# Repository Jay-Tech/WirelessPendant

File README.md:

# Wireless Pendant

Firmware for a wireless handwheel pendant for a grblHAL machine, and for the
receiver board that carries it to the PC. The sender application it talks to is
a separate project — [Jay-Tech/GrblHAL-Sender](https://github.com/Jay-Tech/GrblHAL-Sender),
whose [Wireless Pendant](https://github.com/Jay-Tech/GrblHAL-Sender#wireless-pendant)
section covers the settings at that end. What crosses between them is
[the wire protocol](micropython/pendant/protocol.py) — newline-delimited JSON,
the same either way it travels.

Two boards, both **ESP32-S3**:

| | |
|---|---|
| **pendant** | the handheld — encoder wheel, touch screen, battery. Waveshare ESP32-S3-Touch-LCD-3.5 |
| **receiver** | plugs into the sender's PC, presents a serial port, talks ESP-NOW to the pendant |

The pendant reaches the sender two ways. Over **ESP-NOW** it talks to the
receiver board, which needs no network and no credentials — this is the one it
is built around, because an open-source pendant cannot require the builder to
have usable WiFi in their shop. Over **WiFi** it joins the shop network and
opens a TCP session to the sender directly; that path stays because it is the
reference every jog constant was fitted against.

New board? → [Setting up a board](#setting-up-a-board). One command.

## The hardware

Three things, and none of them is a breadboard any more: an all-in-one host
board, a passive PCB that breaks its header out, and a printed enclosure. All of
it lives under [`hardware/`](hardware/).

| | | |
|---|---|---|
| **host board** | bought | [Waveshare ESP32-S3-Touch-LCD-3.5](https://www.waveshare.com/esp32-s3-touch-lcd-3.5.htm?sku=30733) — MCU, display, touch, PMIC and radio on one board |
| **PSB v1.0** | [`hardware/PendantPcb/`](hardware/PendantPcb/) | breaks that board's 32-pin header out to the handwheel and the three buttons. Carries no components at all |
| **enclosure** | [`hardware/CADandSTL/`](hardware/CADandSTL/) | Fusion 360 sources and printable STLs — the handheld, and a dock for it |

**The bill of materials is five orderable items, with no passives at all:** the
host board, an MPG handwheel, three tactile switches, a LiPo cell, and whatever
the printer eats. A 5 V boost module and the encoder's 22 kΩ divider pair were
both on that list until 2026-08-15 and were measured off it rather than reasoned
off it — [platform-decision.md](hardware/platform-decision.md) carries the
numbers, and [Encoder wiring](#encoder-wiring) below keeps the divider material
for the Pico build and for characterising an unknown wheel.

### The host board

[Waveshare ESP32-S3-Touch-LCD-3.5](https://www.waveshare.com/esp32-s3-touch-lcd-3.5.htm?sku=30733),
SKU 30733.

| | |
|---|---|
| MCU | ESP32-S3R8, dual Xtensa LX7 @ 240 MHz |
| Memory | 512 KB SRAM + **8 MB octal PSRAM**, 16 MB flash |
| Display | 3.5" IPS, 320 x 480, ST7796 over SPI |
| Touch | FT6336U, I²C `0x38`, polled |
| Power | **AXP2101** — charger, power path, fuel gauge and power button in one part, switching rather than linear |
| Battery | 3.7 V LiPo on an MX1.25 header, plus a separate SH1.0 header for an RTC cell |
| Radio | WiFi 4 (2.4 GHz) + BLE 5 on an onboard antenna, **with an IPEX pad for an external one** |
| Unused here | PCF85063 RTC, QMI8658 IMU, ES8311 codec, mic, speaker header, TF slot, camera header |
| Break-out | one 32-pin, 2.54 mm header — which is what PSB v1.0 mates to |

Two of those are why the board won. The **IPEX connector** — reached by
resoldering one resistor — is worth more on a handheld carried around a steel
machine than any latency figure measured here, and the Pico 2 W's antenna is
fixed. The **AXP2101** does in one part what the Pico build needed a LiPo Amigo
Pro and its wiring to do. The 8 MB PSRAM is enough for a full 320x480x2
framebuffer, which is also why the committed MicroPython build is the
`SPIRAM_OCT` variant rather than the plain one — see [ESP32-S3](#esp32-s3).

**The pin map is not in Waveshare's wiki and cannot be read off their schematic
PDF.** It came from their demo code, examples 08 and 11, which agree — and three
of the pins turn out not to be pins:

- **The LCD has no chip select.** The panel is permanently selected, so
  `st7796.py` has to tolerate `cs=None` rather than toggle something that does
  not exist.
- **LCD reset is an I²C write**, to a **TCA9554 expander at `0x20`** that is not
  in the board's advertised feature list and answers writes but not reads. The
  driver takes a reset *callable* instead of a pin, so the caller supplies either
  a pin toggle or an expander write and the driver stays portable.
- **Touch breaks out neither INT nor RST**, and needs neither, being polled.

Everything else transferred intact — the ST7796 init sequence, MADCTL, `INVON`,
the framebuffer push, and the whole of `screen.py` including the portrait layout,
the DRO digits, the step grid and the probe page. USB-C sits at the bottom edge,
which is where the reference pendant puts its cable, so the enclosure works with
it rather than against it.

An I²C scan of the board reads `0x18` ES8311, `0x20` TCA9554, `0x34` AXP2101,
`0x38` FT6336U, `0x51` PCF85063, `0x6b` QMI8658. That AXP2101 at `0x34` is also
how [`setup.py`](tools/setup.py) tells a pendant from a receiver, since the two
enumerate identically over USB — and it reads the chip ID rather than pinging the
address, so something else answering there is not mistaken for a battery.

> **The AXP2101's fuel gauge is not to be trusted on this board**, and the
> pendant does not use it. See [Battery and backlight](#battery-and-backlight)
> for what it did and what replaced it.

### PSB v1.0 — the breakout PCB

[`hardware/PendantPcb/`](hardware/PendantPcb/) is the KiCad project, with the fab
output in [`production/`](hardware/PendantPcb/production/).
[daughter-board.md](hardware/daughter-board.md) is the spec and the argument
behind it.

**It is built, and the pendant runs on it** — this is a board in service rather
than a drawing. The only difference between the fabricated boards and what is in
the repo is the silkscreen: they were made before the `PSB v1.0` version marking
was added, so they carry the functional labels and no revision. Nothing
electrical differs.

It exists because the host board brings almost everything out on that one
header, so a single mating board reaches every signal the pendant needs. The
alternative is seven flying leads soldered to a header, in a tool that gets
carried around a shop.

**Seven signals, and no components.** The move to a 3V3 encoder removed the last
two resistors it would have carried.

| Net | GPIO | J2 pin | Goes to |
|---|---|---|---|
| Encoder A | **9** | 14 | J3 pin 3 — direct, no resistor |
| Encoder B | **10** | 12 | J3 pin 4 — direct, no resistor |
| Encoder Vcc | — | 32 | J3 pin 1. **+3V3, measured 3.29 V — not 5 V, not VBAT** |
| Encoder 0V | — | 4, 30 | J3 pin 2 |
| `feed_hold` | **38** | 7 | SW1, silkscreened `HOLD` |
| `cycle_start` | **39** | 9 | SW2, silkscreened `START` |
| `zero_axis` | **40** | 11 | SW3, silkscreened `ZERO`, long hold |

The GPIO column was measured on the assembled handheld, 2026-08-16, and matches
`BUTTON_MAP` and `ENCODER_PIN_A/B` in
[`pendant.py`](micropython/pendant/pendant.py) — which is the authority. If
either moves, both have to. Buttons are active low against the S3's internal
pull-ups, with no external pull-ups and no debounce parts;
[`buttons.py`](micropython/pendant/buttons.py) debounces in software and has done
since the Pico build.

**Pin 32 is the one worth a meter.** The whole 3V3 encoder decision rests on it
being a regulated rail: the wheel is open-collector, so its outputs swing to
whatever supplies it, and they reach GP9 and GP10 with nothing in the way. On
VBAT or VBUS that is over the S3's ~3.6 V absolute maximum. 3.29 V says it is the
right rail.

**54.50 x 100.00 mm**, 2 mm chamfers on all four corners, and four drill groups —
which is the acceptance test, because anything outside the set is then visible at
a glance:

| Diameter | Plating | Count | |
|---|---|---|---|
| 0.300 | PTH | 2 | vias |
| 1.000 | PTH | 36 | 32 header + 4 encoder |
| 1.300 | PTH | 6 | three switches, two pads each |
| 2.200 | NPTH | 6 | mounting |

A missing 1.300 group means the switches were placed after the export — which
happened, and produced a zip with no buttons on it at all.

Two things on the board are deliberate traps, and both are cheap to check:

- **`+BATT` at J2 pin 1 is a single-node net** — that pad and nothing else on the
  board. Mate the boards and probe it: battery voltage means the numbering
  composes correctly through symbol, footprint and placement; 0 V or 3.3 V means
  one of those three mirrors did not cancel. Safe to probe precisely because
  nothing else is on it.
- **J3 has no keying**, and carries 3V3 and GND adjacent to each other. A cable
  fitted backwards puts reverse polarity across the wheel, so the `+ - A B`
  silkscreen and the pin 1 mark are load-bearing rather than decorative.

The three switches sit **19.0 mm apart, centred on the board's own centreline**.
The first layout had them at 19.5 and 18.5 with the middle one 0.5 mm off, and
unequal spacing between three caps is visible every time once the enclosure is
on.

A **reverse-polarity guard** for the battery is a second, smaller board. It shares
no net with PSB v1.0, which is why it is not on it, and
[daughter-board.md](hardware/daughter-board.md) has the circuit, what to buy, and
how to prove it before it meets the host board. Its KiCad project is gitignored,
so that specification is the only copy of it a clone gets.

### Printed parts

[`hardware/CADandSTL/`](hardware/CADandSTL/). Each folder holds one Fusion 360
file and the STLs exported from it — the `.f3d` is the source and the thing to
edit, the STLs are what a slicer wants. Sizes below are each mesh's measured
bounding box.

**The handheld** — [`Pendant/`](hardware/CADandSTL/Pendant/), from `Pendant.f3d`:

| File | Size, mm | |
|---|---|---|
| `Pendant.stl` | 70.00 x 27.65 x 186.00 | the body |
| `PcbCover.stl` | 54.70 x 3.16 x 100.00 | closes over PSB v1.0 — the footprint is that board's 54.50 x 100.00 plus clearance |
| `BatteryCover.stl` | 65.60 x 8.50 x 75.16 | the cell bay |
| `Button1.stl` | 10.80 x 10.64 x 8.80 | a cap for one of the three switches |
| `Button3.stl` | 10.80 x 10.64 x 8.80 | same envelope, different geometry |
| `ButtonUsbV2.stl` | 13.00 x 10.54 x 8.80 | the wider cap |
| `PowerButton.stl` | 8.39 x 3.60 x 4.60 | reaches the AXP2101's power button through the shell |

**The dock** — [`Mount/`](hardware/CADandSTL/Mount/), from `Mount.f3d`:

| File | Size, mm | |
|---|---|---|
| `Mount.stl` | 82.00 x 37.09 x 102.00 | the cradle the pendant sits in |
| `MountBase.stl` | 82.00 x 37.09 x 10.00 | its base, same footprint |
| `MountUsb.stl` | 20.00 x 20.00 x 5.90 | carries the USB-C end |
| `MountUsbLock.stl` | 11.70 x 6.10 x 17.70 | retains it |

**The body is 186 mm in its longest axis**, so it wants a bed with at least that
much in one direction — a 220 mm printer is fine, a 180 mm one is not.

**The button caps are one dimension chain, not three independent choices.** The
header fixes PSB v1.0's position relative to the host board in all three axes,
and the caps have to reach the enclosure top from there — so board stack height,
switch height and cap height are a single sum. The requirement the caps are cut
against is that each one **bottoms on the enclosure** at the end of its stroke
rather than on the switch, so the switch never takes the force of a gloved thumb,
and that the plunger is guided by a bore in the shell rather than by a spacer
resting on the board. [daughter-board.md](hardware/daughter-board.md) has the
reasoning; `Pendant.f3d` is where to check it.

## Why there is a Pico in here

The project started on a Raspberry Pi Pico 2 W, and that board is still on the
bench as `pico` — it is the reference the ESP32 gets compared against when
something feels wrong, which is why the notes below are kept rather than
deleted. Nothing shipping runs on it.

## Pico 2 W board notes

| | |
|---|---|
| MCU | RP2350, dual Cortex-M33 @ 150 MHz **or** dual Hazard3 RISC-V |
| RAM / flash | 520 KB SRAM / 4 MB QSPI |
| PIO | 3 blocks, 12 state machines |
| Radio | WiFi 4 (802.11n, 2.4 GHz) + Bluetooth 5.2 |
| Power | 1.8-5.5 V into VSYS via onboard buck-boost |

Three things that bite people on this specific board:

- **The onboard LED is not a GPIO.** It hangs off the CYW43 radio chip, so it's
  `Pin("LED")`, never `Pin(25)`. Most Pico tutorials assume a non-W board and
  will silently do nothing.
- **GP29 belongs to the WiFi SPI**, so the usable ADC channels are GP26/27/28
  (channels 0-2). Channel 4 is the internal temperature sensor.
- **Erratum RP2350-E9.** On the A2 stepping, an input pin can latch near 2.15 V
  instead of reading low, and the internal pull-downs are too weak to fix it.
  This hits PIO input programs too. Use an external pull-down of 8.2 kΩ or
  smaller. Stepping A4 corrects it — worth checking which one your board has
  before you spend an evening debugging a "broken" input.

## Setting up a board

```bash
python tools/setup.py
```

One command from a blank ESP32-S3 to a working pendant or receiver. It asks
what you are setting up, finds the board, flashes MicroPython if the board
needs it, checks the hardware matches the role, collects the WiFi and transport
settings, installs, restarts the board and reads back what it says on the way
up.

```bash
python tools/setup.py --pendant     # the handheld
python tools/setup.py --receiver    # the board at the sender's PC
python tools/setup.py --list        # what is attached, and what each one is
```

It replaces the two steps that used to be source edits: `BOARDS` in
[`tools/board.py`](tools/board.py) and a hand-filled `secrets.py`. **If you are
building this for the first time, this is the only thing you need to run** —
everything below is the manual equivalent, kept because it is what to fall back
on when a step misbehaves.

Two things worth knowing about how it finds boards:

- **It never opens a device it has not identified.** Only two USB descriptors
  are eligible — MicroPython on an S3 and on a Pico. Everything else is listed
  and skipped, and a grblHAL controller is named in that listing so you can see
  it was seen and left alone. This matters more than it sounds: `mpremote
  connect auto` once grabbed the STM32 controller on this bench and sent it
  raw-REPL bytes with a machine powered.
- **Each board records what it is**, in a `device.json` written at setup. That
  is what lets a board be found without an entry in `BOARDS`, and it is what
  `sync_board.py --receiver` now checks before it will write `receiver.py` over
  a `main.py` — the pendant and the receiver are both ESP32-S3 and enumerate
  identically, so before this the only guard was a name in a table that a new
  build had not filled in yet.

A pendant board is told apart from a receiver by the **AXP2101 power chip** at
I²C `0x34`, which the pendant carries and a bare receiver does not — and the
chip ID is read rather than the address pinged, so something else answering at
that address is not mistaken for a battery.

Set the receiver up on the sender's PC and it will offer to write the port into
the sender's own config. The sender still never scans for that port itself,
deliberately — see `PendantConfig` for why. This is not scanning; it just
flashed the board and knows where it is.

## Flashing MicroPython

The manual path, and the reference for what `setup.py` does.

### Pico 2 W

1. Download the Pico 2 W `.uf2` from
   [micropython.org/download/RPI_PICO2_W](https://micropython.org/download/RPI_PICO2_W/)
   — take whatever is current there rather than matching the S3 build committed
   at the root, since the two ports version independently. Make sure it's the
   `RPI_PICO2_W` build —
   the plain `RPI_PICO2` build has no WiFi and the plain `RPI_PICO_W` build is
   for the older RP2040 board.
2. Hold **BOOTSEL** while plugging in USB. The board mounts as a drive named
   `RP2350`.
3. Copy the `.uf2` onto it. The board reboots into MicroPython automatically.

If the board misbehaves after switching between Arm and RISC-V builds, or
between MicroPython and C SDK firmware, flash `flash_nuke.uf2` first to wipe
the flash, then reflash. Leftover filesystem blocks confuse the new firmware.

### ESP32-S3

Both the pendant and the receiver are ESP32-S3s, and neither takes a `.uf2` —
there is no BOOTSEL drive to drag a file onto, so flashing goes over the serial
port with `esptool`. The build this repo runs is committed at the root, and it
is the **`SPIRAM_OCT`** variant — these boards have octal SPIRAM, and the plain
`ESP32_GENERIC_S3` build leaves it unused. That mismatch does not fail at the
flash or at the boot; it surfaces much later as an allocation running out while
the pendant paints its display, which reads as a screen bug.

`setup.py` picks that variant on its own when both are sitting at the root, and
asks when it genuinely cannot tell — two versions of the same variant, say,
which is what a version bump leaves behind.

```bash
python -m pip install esptool
```

Put the board into its ROM bootloader: hold **BOOT**, tap **RESET**, release
**BOOT**. It re-enumerates as `303a:1001`, which `tools/board.py` labels
*"ROM bootloader — esptool, not mpremote"*. In MicroPython it is `303a:4001`
instead, and `esptool` will not talk to that one.

Then find the port it came up on — and look it up again rather than reusing what
it had a moment ago. The bootloader and MicroPython present different USB
descriptors, so Windows renumbers the board every time it is flashed. That is
also why every tool here targets a serial number instead of a COM port.

```bash
python -m esptool --chip esp32s3 --port COM# erase-flash
```

```bash
python -m esptool --chip esp32s3 --port COM# --baud 460800 write-flash -z 0 ESP32_GENERIC_S3-SPIRAM_OCT-<version>.bin
```

Offset `0`, not the `0x1000` the original ESP32 takes.

esptool 5 renamed these from `erase_flash` and `write_flash`; the underscore
forms still run but print a deprecation warning, which in the middle of a flash
reads like a fault. `setup.py` picks the spelling from the installed version.

Reset the board and it comes up in MicroPython with a new serial number. Every
S3 here enumerates identically, so that serial number is what distinguishes a
pendant from a receiver, and every tool resolves through it rather than through a
COM port.

There are two places it can come from. `setup.py` writes a `device.json` **on the
board**, which is what lets a board be recognised with no entry in any table —
prefer that. `BOARDS` in [`tools/board.py`](tools/board.py) is the older path and
still works; every id in it is this bench's, so all of them are wrong for you.
`python tools/board.py` lists what is attached and says so when the configured
board is not among them.

## Running the smoke test

Uses [`mpremote`](https://docs.micropython.org/en/latest/reference/mpremote.html):

```bash
pip install mpremote
```

Commands below invoke it as `python -m mpremote` rather than the bare
`mpremote`. On Windows with Microsoft Store Python, the `Scripts\` directory
holding `mpremote.exe` is not on `PATH`, so the bare command fails with
*"not recognized as the name of a cmdlet"* even though the install succeeded.
The `-m` form sidesteps that and works on every platform. See
[PATH fix](#windows-store-python-path) if you want the short command back.

> ### ⚠️ Do not use `connect auto` on a machine with a CNC controller attached
>
> `auto` connects to the first USB serial device it finds. If a grblHAL
> controller is plugged in, that can be the controller rather than the Pico —
> and mpremote will then send raw-REPL control bytes (`Ctrl-A`/`Ctrl-C`) to
> your machine controller trying to get a Python prompt. It happened here: the
> STM32 board on `0483:5740` got grabbed instead of the Pico and reset.
>
> Target the board explicitly by its unique ID instead. The ID is held in one
> place, [`tools/board.py`](tools/board.py), and every tool resolves through it
> — so there is no serial number to copy from a docstring and mistype. It stays
> correct across COM port renumbering.
>
> Run it to see what is attached and which device is the target. It labels the
> controller so it cannot be picked by accident:
>
> ```bash
> python tools/board.py
> ```
>
> Override it without editing anything by setting `PICO_DEVICE`.
>
> Pico boards report a `2e8a:` vendor ID (`0005` = MicroPython running,
> `000f` = RP2350 BOOTSEL). An STM32 grblHAL board reports `0483:5740`. Use
> the serial number in the second column as `id:<serial>`.

Set up credentials (this file is gitignored — it never reaches a commit):

```bash
cp micropython/secrets.example.py micropython/secrets.py
```

**Edit it before running anything.** Leaving the placeholder SSID in place
makes `wifi_join` fail with `no such network in range`. Then copy it to the
board and run the test:

```bash
python tools/sync_board.py
```

```bash
python tools/on_board.py micropython/smoke_test.py
```

`run` streams the script from your PC rather than installing it, but imports
still resolve on the board — which is why `secrets.py` has to be copied over
first. To drop into the REPL instead:

```bash
python -m mpremote connect $PICO_DEVICE repl
```

To confirm the board is seen at all, and check what it's running:

```bash
python -m mpremote devs
```

A Pico 2 W shows a `2e8a:` vendor ID. PID `0005` means MicroPython is already
flashed and talking; PID `000f` means the board is sitting in RP2350 BOOTSEL
mode waiting for a UF2.

Prefer a GUI? [Thonny](https://thonny.org/) works well: set the interpreter to
*MicroPython (Raspberry Pi Pico)* and it handles the board filesystem for you.

### What it checks

Six stages, each reporting PASS / FAIL / SKIP with a summary at the end:

| Stage | Proves |
|---|---|
| `identity` | firmware, chip ID, clock, heap, filesystem |
| `led` | GPIO path via the CYW43 — visible blink |
| `temp` | ADC works (internal sensor, uncalibrated, ±a few °C) |
| `wifi_scan` | radio powers up and hears networks |
| `wifi_join` | association + DHCP lease |
| `net_io` | DNS + TCP + HTTP, end to end |

The last three need `secrets.py`; without it they report SKIP and the rest
still runs, so the script is useful before you've picked a network.

Two of those stages are Pico-shaped: `led` goes through the CYW43 radio chip
rather than a GPIO, and `temp` reads the RP2350's internal sensor. Both are
board-level proof of life rather than anything the pendant depends on — on an S3
the equivalent bring-up is
[`selftest_board.py`](micropython/pendant/selftest_board.py) and the per-subsystem
self-tests under [Pendant hardware summary](#pendant-hardware-summary).

## Pendant hardware summary

Every pin the pendant uses, in one place — the part you want with a soldering
iron in your hand. Why each one is where it is: [The hardware](#the-hardware)
above, and the design notes below.

**Discrete parts: none.** Nothing sits between the host board and the
peripherals — no level shifters, no pull-ups, no dividers, no transistors. The
encoder's 22 kΩ pair left with the move to 3V3, and the display and touch panel
are on the host board rather than wired to it.

| GPIO | Net | Notes |
|---|---|---|
| GP9 | encoder A | direct, no resistor |
| GP10 | encoder B | direct, no resistor |
| GP38 | feed hold | to GND, internal pull-up |
| GP39 | cycle start | to GND, internal pull-up |
| GP40 | zero axis | to GND, internal pull-up, long hold |
| GP1 / GP2 / GP5 | LCD MOSI / MISO / SCK | SPI2, all on the host board |
| GP3 | LCD DC | |
| GP6 | LCD backlight | PWM — see [Battery and backlight](#battery-and-backlight) |
| — | LCD CS | there isn't one; the panel is permanently selected |
| — | LCD RST | TCA9554 at `0x20`, pin 1 |
| GP8 / GP7 | I²C SDA / SCL | I2C0 — touch, PMIC, RTC and IMU all share it |
| **3V3** | encoder Vcc | **not 5 V, not VBAT.** J2 pin 32, measured 3.29 V |
| GND | encoder 0V | J2 pins 4 and 30 |

Deliberately unconnected on PSB v1.0: **J2 pin 2 (VBUS)**, which measures 0 V
without USB and 4.89 V with, and **J2 pin 31 (3V3)**, a second tap on the rail
that pin 32 already supplies.

Axis and step selection live on the touch panel rather than on buttons. Both are
bigger targets than a button and, unlike a button, say what is selected without
being read back off a status line. What stays physical is what has to work
without looking and while a job is running — feed hold and cycle start are the
only pendant commands the sender will forward mid-job, and zeroing is a long
hold because it rewrites the work offset.

> **The Pico 2 W map differs in almost every position**, and is kept because that
> board is still the bench reference. Encoder A/B on **GP2/GP3** through the
> 22 kΩ dividers; buttons on **GP7/GP8/GP9**; touch on I2C1 — SDA **GP10**, SCL
> **GP11**, with INT **GP12** and RST **GP13**; display on SPI0 — SCK **GP18**,
> MOSI **GP19**, DC **GP20**, RST **GP21**, CS **GP17**, backlight **GP22**.
> There the encoder *and* the display both run from **VBUS at 5 V**, which is the
> substantive difference: on the S3 the encoder is on the regulated 3V3 and the
> display is not wired at all. [`pendant.py`](micropython/pendant/pendant.py)
> carries both maps and picks on the port, so nothing above the pin constants
> knows which board it got.

**Bringing a rebuilt harness up**, one layer at a time rather than all at once:

```bash
python tools/on_board.py micropython/pendant/probe_encoder.py      # characterise A/B
python tools/on_board.py micropython/pendant/selftest_pcnt.py      # the S3 decoder
python tools/on_board.py micropython/pendant/selftest_quadrature.py # the Pico decoder
python tools/on_board.py micropython/pendant/selftest_st7796.py    # backlight, then pixels
python tools/on_board.py micropython/pendant/selftest_touch.py     # bus, then part, then touches
python tools/on_board.py micropython/pendant/selftest_link.py
```

Each separates the failures the one above it would otherwise mask. The decoder
self-test is per-port: the S3 counts in PCNT hardware, the Pico uses a hard pin
IRQ, and `pendant.py` chooses between them — a soft IRQ on the ESP32 would sit
behind the interpreter where a display refresh could hold it off long enough to
drop edges.

## Design notes

> **Quietening the pendant for machine work.** Set `TRACE_DUMP_BUDGET = 0` in
> [`micropython/pendant/jog.py`](micropython/pendant/jog.py) to stop the trace
> tables. Everything is still counted and still reported in the periodic
> one-liner, so nothing is lost but the tables.
>
> It matters because printing can block. With no USB host attached MicroPython
> discards console output, so a pendant running standalone from `main.py`
> cannot stall on it however much it writes — but attached to `mpremote`, a
> host that is not draining fast enough blocks `print()`, and a blocked print
> blocks the whole event loop: the socket read and the jog scheduler with it.
> A run with seventy trace dumps stalled the loop for a full second.

A handheld MPG pendant — handwheel, buttons, display — that talks to the
**sender application**, not to the controller:

```
  pendant  --ESP-NOW-->  receiver (USB serial)  --\
                                                   >-- Sender (PC) --> controller
  pendant  --WiFi/TCP------------------------------/
```

Either transport carries the same newline-delimited JSON, so nothing above the
transport — jogging, buttons, the status feed — knows which one a pendant
arrived on.

### Why not straight to the controller

The obvious design — pendant connects directly to the machine over the network —
does not work, for two independent reasons:

- **grblHAL's telnet server accepts exactly one client.** `telnetd.c` refuses a
  second connection outright (`if(session->pcb) return ERR_CONN;`). The sender
  already holds that session, so the pendant cannot have one.
- **On an SLB, the board isn't reachable anyway.** Sienci documents a direct
  PC-to-board Ethernet cable on a static `192.168.5.x` subnet. That link is an
  isolated segment with no route from the WiFi network.

Going through the sender avoids both, works with any controller, and keeps the
sender as the single arbiter of the command queue — which is what GRBL requires
regardless of transport.

### Encoder wiring

> **The RP2350 is not 5 V tolerant.** A 5 V handwheel will damage a GPIO if
> wired straight in. Identify the output type first.

Count the terminals:

| Terminals | Type | Wiring |
|---|---|---|
| **6** — A, B, 0V, Vcc, A-, B- | Differential **line driver**, push-pull, swings a full 0–5 V | Divider on A and B (below), or an RS-422 receiver |
| 4 — A, B, 0V, Vcc | Single-ended; still need to know which kind | Open-collector: 4.7 kΩ pull-up to **3.3 V**. Push-pull: divider as below |

**Six terminals does not automatically mean a line driver.** The wheel used
here has A, B, 0V, Vcc, A-, B- and turned out to be **open-collector with an
internal pull-up**, measured at ~13.3 kΩ. Characterise before wiring:

```bash
python tools/on_board.py micropython/pendant/probe_encoder.py
```

An open-collector output already has a pull-up forming the top leg of a
divider, so adding an external series resistor only drops the level further.
One resistor to ground is the whole circuit:

```
  encoder A ──┬────────────────> GP2
             [22k]
              │
             GND                 (same again for B -> GP3)

  encoder 0V  ──────────────────> GND  (pin 38)
  encoder Vcc ──────────────────> VBUS (pin 40, USB 5 V)
```

4.909 V × 22/(13.3+22) = **3.06 V**. The level has to clear the RP2350's
input-high threshold (~2.15 V) without passing its absolute maximum of
**IOVDD + 0.3 V = 3.6 V**.

| To ground | Level | |
|---|---|---|
| 10k | 2.11 V | fails — below input-high |
| 20k | 2.95 V | works |
| **22k** | **3.06 V** | best centred, tolerant of pull-up variation |

> **Superseded on the ESP32-S3 build, 2026-08-15.** The encoder now runs from
> the regulated 3V3 with **no resistors at all** - simpler, and a better logic
> level than the divider above. The paragraph that used to sit here said
> powering it at 3V3 "is not worth it: the part is specified at 5 V and an
> under-driven encoder that works intermittently is the worst outcome
> available." That was wrong, and is left visible because it failed in an
> instructive way.
>
> It conflated the supply with the interface. The wheel is **open-collector**,
> so its output level is its own supply: at 3V3 the pin sees a clean 3.3 V,
> where the divider above delivers **3.06 V**. The arrangement being defended
> was the more under-driven of the two. The only real question was whether the
> wheel's internals run at 3.3 V, and they do - 16,695 counts at up to 195
> detents/s with nothing dropped.
>
> Two things still matter. **Remove the resistors when you move to 3V3, not
> after**: kept, they divide against the internal pull-up and give ~2.06 V,
> under the input-high threshold on both parts. And **do not take Vcc from the
> battery rail** - the level follows the supply, so it passes the S3's ~3.6 V
> absolute maximum on a charged cell and sags as it drains.
>
> See [hardware/platform-decision.md](hardware/platform-decision.md). The
> divider material above stays for the Pico 2 W build and for characterising an
> unknown wheel.

A- and B- go unused. They exist for noise immunity over a long cable; if
`errors` starts climbing because the lead runs near a VFD or steppers, feed
A/A- and B/B- into a 3.3 V RS-422 receiver (MAX3095 or similar) and take
single-ended 3.3 V out. Not needed for a short bench lead, and PSB v1.0's
4-pin J3 does not land them.

Erratum E9 is not a factor either way here, since the input is actively driven
rather than resting on a weak pull-down.

Defaults are **GP2 = A, GP3 = B** on the Pico and **GP9 = A, GP10 = B** on the
ESP32-S3.

**Check before connecting:** power the encoder from 5 V and GND only, and
measure A against 0V while turning slowly. It should swing hard between ~0 V
and ~5 V. If it never reaches 5 V unaided it is open-collector, not a line
driver, and wants pull-ups instead of dividers.

### Battery and backlight

Both are ESP32-S3 only - they depend on the AXP2101 the board carries.

**Charge is read from the cell voltage, not from the PMIC's fuel gauge.** The
gauge on this board is wrong: at a steady 4.01 V on charge it reported 81%,
then decayed 82% to 59% over thirty seconds, then read 31%. A cell at 4.0 V is
genuinely 75-85%. It reads 0 correctly with no cell, so it is not dead - it is
worse than dead, because every individual reading looks plausible and nothing
about the number says it is wrong.

[`battery_monitor.py`](micropython/pendant/battery_monitor.py) interpolates a
LiPo curve instead. A curve is the cruder instrument and its limits are worth
knowing: it reads high while charging, dips during radio bursts as the cell
sags under load, and is nearly flat between 3.7 and 3.9 V where a few millivolts
move it ten points. It is honest at the ends, which is where a warning has to
be right. The gauge is still logged beside it at boot, so a board where they
agree will say so.

The panel shows it on the link row: grey above 20%, amber to 10%, red below,
and green whenever charging at any level. `--` rather than `0%` when there is
nothing trustworthy to say - no cell, no PMIC, or a reading outside the curve -
because a confident zero reads as flat rather than as unknown.

**The backlight dims to 15% after two minutes idle**, which is most of what the
pendant can do about its own battery: the backlight draws 100-150 mA against
50-120 mA for the CPU and radio together. Dim rather than off, because a dim DRO
can still be read from the machine and a blank one has to be woken before it can
answer the glance that prompted it. Only operator input counts as use - wheel,
touch, buttons - deliberately not machine motion, since a job can run for an
hour with nobody touching the pendant and that is exactly when it is worth
turning down.

```bash
python tools/on_board.py micropython/pendant/selftest_battery.py    # cell to panel
python tools/on_board.py micropython/pendant/selftest_backlight.py  # PWM or on/off
python tools/on_board.py micropython/pendant/probe_axp2101.py       # does a reading hold still
python tools/on_board.py micropython/pendant/probe_axp2101_map.py   # dump, for diffing
python tools/test_battery.py                                        # the curve, no board
```

`selftest_backlight.py` earns its place: the driver falls back to on/off where a
port has no PWM, and that fallback silently turns "dim after two minutes" into
"blank after two minutes". It says which one you actually got.

**Probes here take no input mid-run.** Driven through `mpremote`, output does
not reach you until the run has finished, so a prompt printed during one is read
after it is over. Anything needing hardware moved compares two separate runs
instead - dump, change the thing, dump again, diff. `probe_axp2101_map.py` is
built that way; three earlier attempts at a timed window were lost before that
was understood, and each reported "nothing moved", which is exactly what a real
negative result looks like.

### Network link

[`link.py`](micropython/pendant/link.py) joins WiFi and holds a TCP session to
the sender, reconnecting on its own. The pendant is the client: the sender is
a fixed always-on machine, the pendant is the thing that wanders off and gets
switched off.

Three things it handles that a plain socket does not:

- **Silent death.** A session whose peer vanished — PC asleep, AP dropped —
  stays open for minutes before the stack notices, which on a pendant reads as
  a handwheel that has simply stopped working. A ping every 3 s plus a 10 s
  receive deadline turns that into a fast, visible reconnect.
- **Backpressure.** The send queue is bounded and drops oldest. A pendant that
  can't reach the sender must never build a backlog of stale jog commands that
  all execute at once when the link returns.
- **Flush before close.** Closing a socket discards whatever is still queued,
  so `flush()` exists and any orderly shutdown must call it. Skipping it loses
  the last few messages silently, after they have already been counted as sent.

### ESP-NOW receiver

The other transport, and the one the pendant is moving to. Instead of joining
the shop WiFi it talks ESP-NOW straight to a second ESP32-S3 plugged into the
sender's PC, which presents a serial port. What crosses that port is exactly
what crossed the TCP socket — the same newline-delimited JSON — so the sender
reads a different transport and the protocol itself does not change.

[`micropython/receiver/receiver.py`](micropython/receiver/receiver.py) is the
whole of it, and it is one file with no dependencies: it imports only `sys`,
`select`, `time`, `network` and `espnow`, all built into the ESP32 port. No
`secrets.py` either, since ESP-NOW needs no credentials.

Setting up the receiver is one command, which also does the flashing:

```bash
python tools/setup.py --receiver
```

The manual equivalent, after flashing MicroPython above:

1. See what is attached, and note the board's serial number:

```bash
python tools/board.py
```

2. Set `receiver` in `BOARDS` in [`tools/board.py`](tools/board.py) to that
   `id:`.
3. Install it:

```bash
python tools/sync_board.py --receiver
```

4. Reset or replug the board.

Step 4 is easy to skip and looks like a failure when you do. `mpremote` leaves
the board in the REPL, so `main.py` is installed but not yet running — set one
up in place, look at the port, and a silent port reads as a bad install. Moving
the board to the shop PC resets it anyway, so this only bites when bench-testing
where you flashed it.

Step 3 copies `receiver.py` as `main.py` and nothing else, so the board comes up
on its own when the shop PC powers on, which is the whole point of it. Unlike
the pendant's `--main` there is no opt-in, because there is no development mode
to protect here.

It targets the board named `receiver` and ignores `PICO_DEVICE`. If you keep
more than one — a spare, or a bench board — name the others `receiver2`,
`receiver3` and select them with `--device receiver2`. The prefix is
load-bearing rather than descriptive: this refuses to run against a board whose
name does not begin `receiver`. Every S3 enumerates identically, so that name is
the only guard against writing the receiver's entry point over the pendant's — a
mistake that is silent at the time and shows up later as a pendant that does
nothing.

To watch it run without installing it:

```bash
python tools/on_board.py micropython/receiver/receiver.py --device receiver2 --no-sync
```

`--no-sync` matters: without it `on_board.py` copies the pendant's modules
first, which the receiver neither imports nor needs.

Pairing takes no configuration. The pendant broadcasts until something answers;
the receiver learns its MAC from the first packet and unicasts back. A pendant
that reboots keeps its MAC, so the receiver also answers a familiar peer that
has gone quiet — without that it would ignore the rebooted pendant's broadcasts
and never re-pair.

The receiver writes its own diagnostics into the same stream as
`{"t":"rx_note","msg":...}` rather than as bare prints, which would land
mid-protocol and read as a malformed line. The sender shows them as
`[Pendant] Receiver: …`. On power-up you should see:

```
{"t":"rx_note","msg":"receiver up, this board is 68:EE:8F:50:B2:84"}
```

and the pendant's MAC when one pairs. Those two lines are what to look at when
pairing is not working.

Only one thing may hold the port. The sender, `mpremote` and
[`tools/espnow_bridge.py`](tools/espnow_bridge.py) all open it exclusively, so
`sync_board.py` reporting *"could not read the board"* usually means the sender
is running. The bridge is retired now that the sender reads the port itself, and
must not be left running alongside it.

### Mock sender

[`tools/mock_sender.py`](tools/mock_sender.py) stands in for the real sender:
it accepts a pendant, applies incoming jogs to a simulated DRO, and streams
status back at 10 Hz. Turn the handwheel and the position moves.

```bash
python tools/mock_sender.py --verbose
```

Then, with `SENDER_HOST` set in `secrets.py`:

```bash
python tools/on_board.py micropython/pendant/selftest_link.py
```

The self-test drives synthetic handwheel motion — an out-and-back sweep on X, a
one-way Z move, buttons — and checks the DRO the sender reports back actually
follows. It needs no encoder or display wired.

### Running it

```bash
python tools/run_pendant.py
```

Syncs the board then starts the pendant. Both steps in one because forgetting
either is silent and misleading: no sync runs stale modules, and no run looks
exactly like a pendant that is broken rather than one that was never started.

`run_pendant.py` syncs the modules but not the entry point, so a board driven
this way still boots to a free REPL. Installing `pendant.py` as `main.py` is a
separate, deliberate step — `sync_board.py --main` does it, and
[`setup.py`](tools/setup.py) passes that flag for you, so **a pendant brought up
by `setup.py` does run at power-up**, which is the point of a pendant.

`main.py` is kept out of the sync's module list on purpose: otherwise every
development run would also change what the board does when it is next switched
on. The cost is that a board can sit with every module current and an entry point
months old — which happened, and ran for weeks with a `main.py` from before the
battery work while `axp2101.py`, `battery_monitor.py` and `screen.py` were all up
to date beside it. The panel showed `--` for charge, so it read as a hardware
fault rather than a stale file. `sync_board.py` now hash-checks the installed
entry point against `pendant.py` even when it is not installing it, and says when
the two differ.

The other cost is the REPL: `main.py` holds it from boot, so recovering a board
that fails inside the pendant means catching the gap before the script starts, or
reflashing. An escape hatch — skip startup if a button is held — is still worth
having and does not exist yet.

### Jog behaviour — open question

Two philosophies, and which feels right is a question for a real machine:

- **Velocity-follow** (current default). Stopping the wheel flushes queued
  motion and halts. The machine never runs on past your hand. Ten fast clicks
  may travel less than ten steps' worth, because the remainder is cancelled.
- **Queue-and-execute.** Every detent is honoured exactly, so ten clicks is
  always ten steps. The machine lags a fast spin and keeps moving after you
  stop.

Velocity-follow is the default because a handwheel is used to position by eye —
if you want an exact distance you would type it. Step size (the two step
buttons) is the coarse/fine control, which may well cover the "spin fast for
rough distance, crawl for fine" need without a second mode.

Compare them on a running pendant without reflashing:

```python
scheduler.cancel_on_stop = False   # queue-and-execute
scheduler.cancel_on_stop = True    # velocity-follow
```

The cancel threshold is `IDLE_MS_BEFORE_CANCEL`, 300 ms. It has to clear a slow
turn: someone winding continuously still produces a detent every few hundred
ms, and a shorter threshold fires between individual detents and truncates jogs
mid-move.

### Verifying the decoder

Decode logic runs on a PC with no board attached — it stubs `machine` and
drives the real class, so the test can't drift from the code:

```bash
python tools/test_quadrature.py
```

The hardware path (pin config, hard IRQ dispatch, speed headroom) needs two
jumpers, GP16→GP2 and GP17→GP3, which synthesise quadrature and read it back:

```bash
python tools/on_board.py micropython/pendant/selftest_quadrature.py
```

It reports where edges start getting missed. A hand-turned 100 PPR wheel peaks
around 2000 edges/s, so there should be a lot of margin above it.

## Windows Store Python PATH

Optional — only if you want to type `mpremote` instead of `python -m mpremote`.

Microsoft Store Python installs console scripts into a sandboxed per-user
directory that the Store's PATH shim doesn't cover. Find it with:

```bash
python -c "import sysconfig; print(sysconfig.get_path('scripts', 'nt_user'))"
```

Then append that one directory to your **user** PATH (this reads and writes
only the user scope, so it can't clobber the machine PATH):

```powershell
$s = python -c "import sysconfig; print(sysconfig.get_path('scripts','nt_user'))"; [Environment]::SetEnvironmentVariable('Path', [Environment]::GetEnvironmentVariable('Path','User') + ';' + $s, 'User')
```

Restart the terminal afterwards. Existing sessions keep the old PATH.

## Layout

```
micropython/
  pendant/              everything the handheld runs
    pendant.py            the program; installed as main.py
    jog.py                detents -> motion. The hard-won one; see the warning below
    protocol.py           the wire format, shared with the sender
    link.py               WiFi transport - joins, holds a TCP session, reconnects
    espnow_link.py        ESP-NOW transport - broadcasts until a receiver answers
    screen.py touch.py    UI, on ili9341.py / st7796.py / tca9554.py
    quadrature*.py        encoder decoding, PIO and PCNT variants
    axp2101.py            power chip: battery voltage and charge state
    battery_monitor.py    what the screen shows, off the above
    selftest_*.py         one per subsystem, streamed with on_board.py
  receiver/
    receiver.py           the whole receiver; installed as main.py
  secrets.example.py    template -> secrets.py, or let setup.py write it
  smoke_test.py         staged board bring-up check

tools/                  run from the repo root, never on the board
  setup.py              blank board -> working pendant or receiver
  board.py              which board is which, and what is safe to talk to
  sync_board.py         copy modules to a board, hash-compared
  on_board.py           stream a script to a board and watch it run
  mock_sender.py        stands in for the sender: accepts a pendant, moves a DRO
  replay_pendant.py     re-run a captured session against the jog logic
  test_*.py             host-side tests, no board needed

hardware/
  platform-decision.md  why this board and this link, with the measurements
  daughter-board.md     PSB v1.0: every net, the header mapping, as-built numbers
  carrier-board.md      the superseded Pico carrier, kept for its mechanical work
  PendantPcb/           KiCad for PSB v1.0; production/ is the fab output
  CADandSTL/
    Pendant/              body, covers and button caps - Pendant.f3d plus STLs
    Mount/                the dock - Mount.f3d plus STLs
  Outline.dxf Holes.dxf  board geometry out of Fusion, for KiCad to import
```

**Two hardware directories exist on the bench but not in a clone.** `.gitignore`
excludes the KiCad export (`hardware/PendantPcbExport`) and the reverse-polarity
guard's own project (`hardware/ReversePolarityPcb/PolarityProtector`), so neither
travels — the guard's specification in
[daughter-board.md](hardware/daughter-board.md) is the copy that does.

Credentials live in `secrets.py`, which is gitignored — `setup.py` writes it, or
copy `secrets.example.py` by hand. The example is tracked, so keep the
placeholders in it and never put real values there.

> **`jog.py` is not to be edited casually.** Its constants were fitted against
> a real machine over several sessions, and its comments record the attempts
> that failed. It also sits in series with a second rate regulator at the
> sender end, so a change here reacts to a change there. Read
> [Jog behaviour](#jog-behaviour--open-question) first.

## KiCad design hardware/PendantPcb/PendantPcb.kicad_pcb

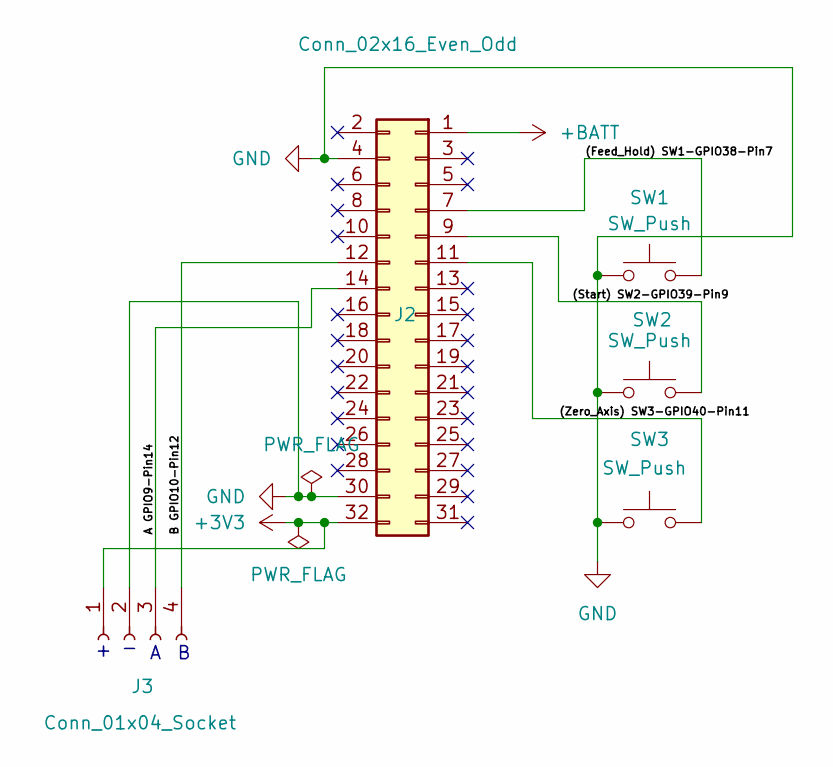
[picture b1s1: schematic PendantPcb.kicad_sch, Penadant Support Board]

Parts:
J2: Conn_02x16_Even_Odd; PinHeader_2x16_P2.54mm_Vertical_Left
J3: Conn_01x04_Socket; PinHeader_1x04_P2.54mm_Horizontal
SW1, SW2, SW3: SW_Push; SW_PUSH_1P1T_6x3.5mm_H4.3_APEM_MJTP1243

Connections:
+3V3: J2.32, J3.1
+BATT: J2.1
/(Feed_Hold) SW1-GPIO38-Pin7: J2.7, SW1.1
/(Start) SW2-GPIO39-Pin9: J2.9, SW2.1
/(Zero_Axis) SW3-GPIO40-Pin11: J2.11, SW3.1
/A GPIO9-Pin14: J2.14, J3.3
/B GPIO10-Pin12: J2.12, J3.4
GND: J2.4, J2.30, J3.2, SW1.2, SW2.2, SW3.2

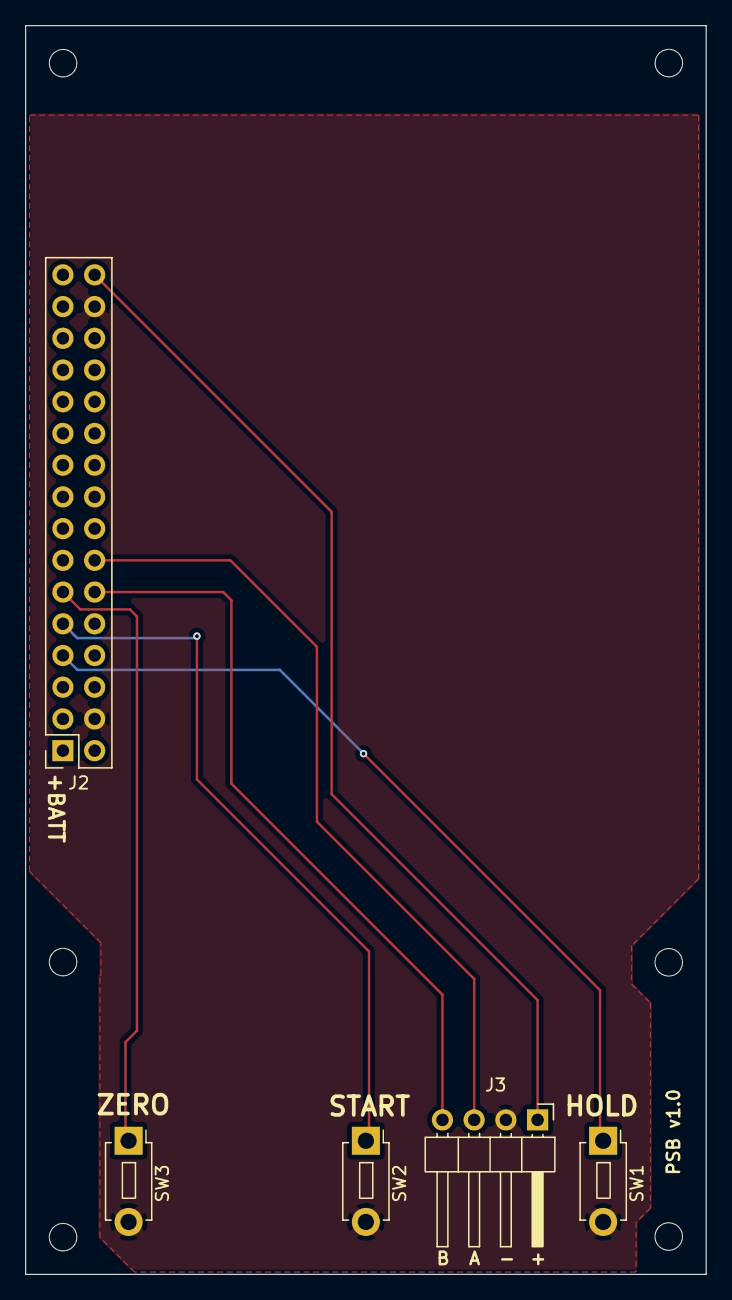
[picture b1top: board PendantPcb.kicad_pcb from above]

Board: 2 copper layers, 54.5 x 100.0 mm, 5 parts (0 on the bottom side), 7 nets.

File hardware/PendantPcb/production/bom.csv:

Designator,Footprint,Quantity,Value,LCSC Part #
J2,PinHeader_2x16_P2.54mm_Vertical_Left,1,Conn_02x16_Even_Odd,
J3,PinHeader_1x04_P2.54mm_Horizontal,1,Conn_01x04_Socket,
"SW1, SW2, SW3",SW_PUSH_1P1T_6x3.5mm_H4.3_APEM_MJTP1243,3,SW_Push,
